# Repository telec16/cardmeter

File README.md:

# Cardmeter

The pleasure of having a multimeter in your pocket !

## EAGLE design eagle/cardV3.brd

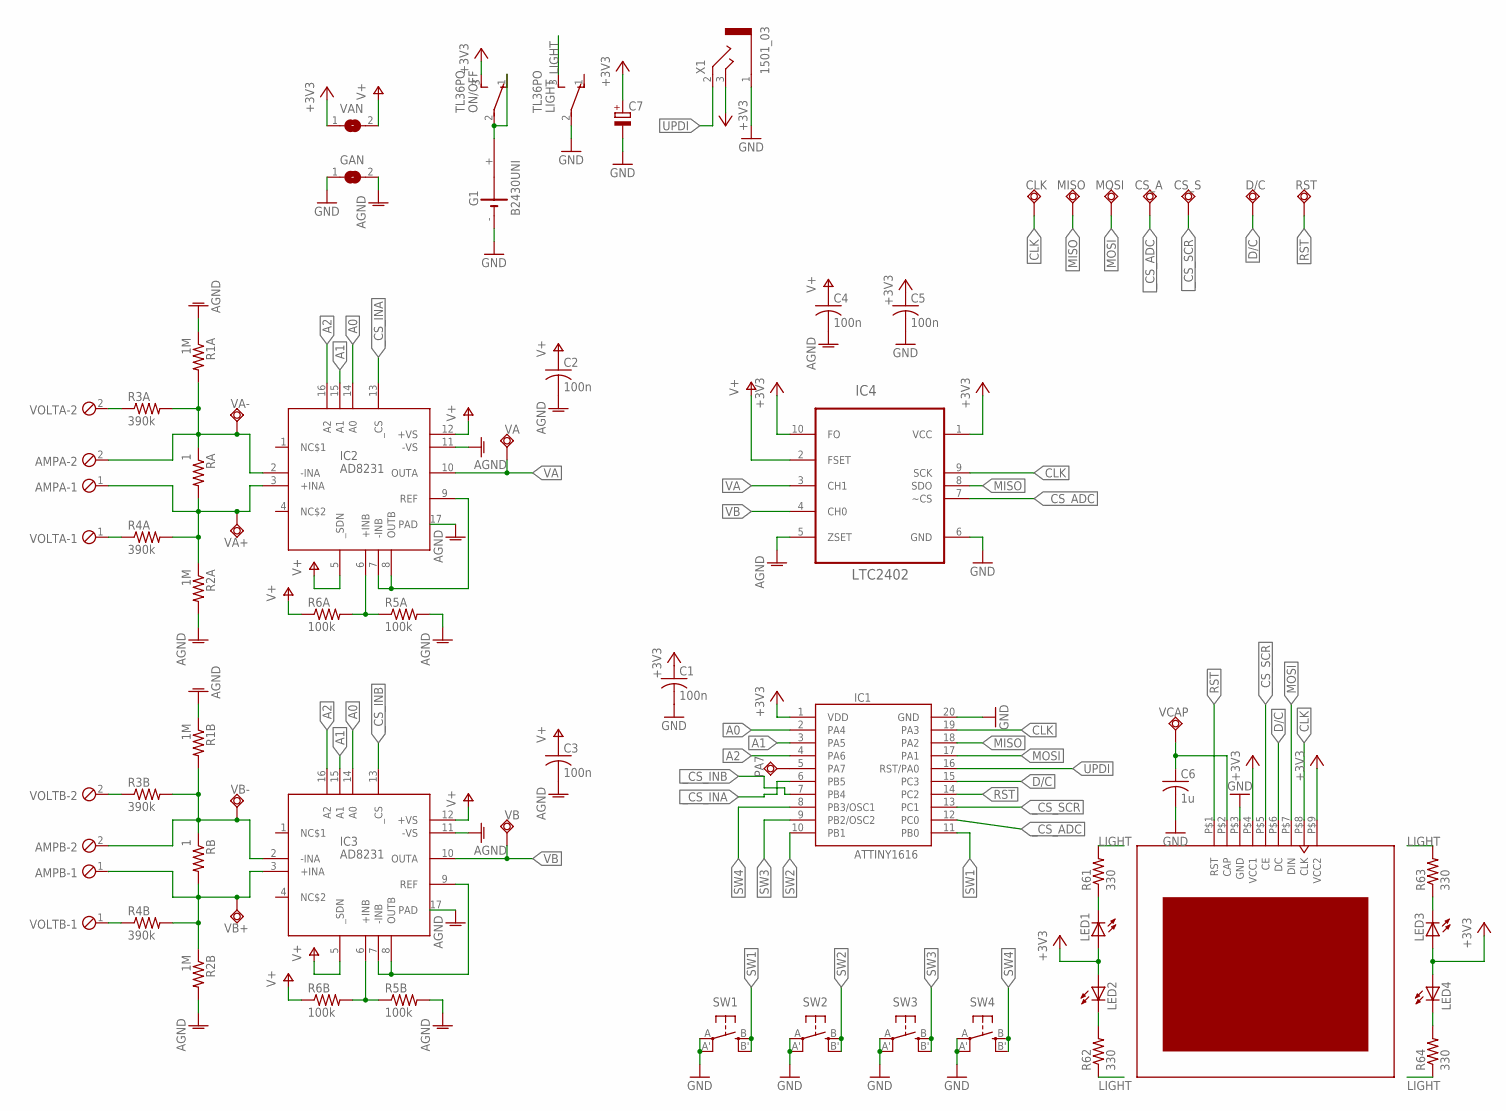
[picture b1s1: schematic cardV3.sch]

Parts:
AMPA: MPT2; 2POL254
AMPB: MPT2; 2POL254
C1, C2, C3, C4, C5: 100n; C0805K
C6: 1u; C0805
C7: CPOL-EU153CLV-0405; 153CLV-0405
CLK: TPSQB1,27; B1,27
CS_A: TPSQB1,27; B1,27
CS_S: TPSQB1,27; B1,27
D/C: TPSQB1,27; B1,27
G1: B2430UNI
GAN: SJ
IC1: ATTINY1616; SO20W
IC2, IC3: AD8231; LFCSP16
IC4: LTC2402; MSOP10
LED1, LED2, LED3, LED4: LEDCHIP-LED0805; CHIP-LED0805
LIGHT: TL36PO; TL3XPO
MISO: TPSQB1,27; B1,27
MOSI: TPSQB1,27; B1,27
ON/OFF: TL36PO; TL3XPO
PA7: TPSQB1,27; B1,27
R1A, R1B, R2A, R2B: 1M; M0805
R3A, R3B, R4A, R4B: 390k; M0805
R5A, R5B, R6A, R6B: 100k; M0805
R61, R62, R63, R64: 330; M0805
RA: 1; M0805
RB: 1; M0805
RST: TPSQB1,27; B1,27
SCR: NOKIA_SCREEN
SW1, SW2, SW3, SW4: SPST_TACT-EVQQ2; EVQ-Q2
VA: TPSQB1,27; B1,27
VA+: TPSQB1,27; B1,27
VA-: TPSQB1,27; B1,27
VAN: SJ
VB: TPSQB1,27; B1,27
VB+: TPSQB1,27; B1,27
VB-: TPSQB1,27; B1,27
VCAP: TPSQB1,27; B1,27
VOLTA: MPT2; 2POL254
VOLTB: MPT2; 2POL254
X1: 1501_03

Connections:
+3V3: C1.1, C5.1, C7.+, IC1.1 (VDD), IC4.1 (VCC), IC4.10 (FO), LED1.A, LED2.A, LED3.A, LED4.A, ON/OFF.3 (S), SCR.P$4 (VCC1), SCR.P$9 (VCC2), VAN.1, X1.3
A0: IC1.2 (PA4), IC2.14 (A0), IC3.14 (A0)
A1: IC1.3 (PA5), IC2.15 (A1), IC3.15 (A1)
A2: IC1.4 (PA6), IC2.16 (A2), IC3.16 (A2)
AGND: C2.2, C3.2, C4.2, GAN.2, IC2.11 (-VS), IC2.17 (PAD), IC3.11 (-VS), IC3.17 (PAD), IC4.5 (ZSET), R1A.1, R1B.1, R2A.2, R2B.2, R5A.2, R5B.2
CLK: CLK.TP, IC1.19 (PA3), IC4.9 (SCK), SCR.P$8 (CLK)
D/C: D/C.TP, IC1.15 (PC3), SCR.P$6 (DC)
GND: C1.2, C5.2, C6.2, C7.-, G1.-, GAN.1, IC1.20 (GND), IC4.6 (GND), LIGHT.2, SCR.P$3 (GND), SW1.A, SW1.A' (P1), SW2.A, SW2.A' (P1), SW3.A, SW3.A' (P1), SW4.A, SW4.A' (P1), X1.1
LIGHT: LIGHT.3 (S), R61.2, R62.1, R63.2, R64.1
MISO: IC1.18 (PA2), IC4.8 (SDO), MISO.TP
MOSI: IC1.17 (PA1), MOSI.TP, SCR.P$7 (DIN)
unnamed: G1.+, ON/OFF.1 (O), ON/OFF.2
unnamed: LED1.C, R61.1
unnamed: C6.1, SCR.P$2 (CAP), VCAP.TP
unnamed: LED2.C, R62.2
unnamed: LED4.C, R64.2
unnamed: LED3.C, R63.1
unnamed: R4A.1, VOLTA.1
unnamed: AMPB.2, IC3.2 (-INA), R1B.2, R3B.2, RB.1, VB-.TP
unnamed: AMPB.1, IC3.3 (+INA), R2B.1, R4B.2, RB.2, VB+.TP
unnamed: IC2.6 (+INB), R5A.1, R6A.2
unnamed: R3A.1, VOLTA.2
unnamed: AMPA.2, IC2.2 (-INA), R1A.2, R3A.2, RA.1, VA-.TP
unnamed: IC2.7 (-INB), IC2.8 (OUTB), IC2.9 (REF)
unnamed: AMPA.1, IC2.3 (+INA), R2A.1, R4A.2, RA.2, VA+.TP
unnamed: R3B.1, VOLTB.2
unnamed: IC3.7 (-INB), IC3.8 (OUTB), IC3.9 (REF)
unnamed: R4B.1, VOLTB.1
unnamed: IC3.6 (+INB), R5B.1, R6B.2
unnamed: IC1.5 (PA7), PA7.TP
RST: IC1.14 (PC2), RST.TP, SCR.P$1 (RST)
SW1: IC1.11 (PB0), SW1.B (S), SW1.B' (S1)
SW2: IC1.10 (PB1), SW2.B (S), SW2.B' (S1)
SW3: IC1.9 (PB2/OSC2), SW3.B (S), SW3.B' (S1)
SW4: IC1.8 (PB3/OSC1), SW4.B (S), SW4.B' (S1)
UPDI: IC1.16 (RST/PA0), X1.2
V+: C2.1, C3.1, C4.1, IC2.5 (_SDN), IC2.12 (+VS), IC3.5 (_SDN), IC3.12 (+VS), IC4.2 (FSET), R6A.1, R6B.1, VAN.2
VA: IC2.10 (OUTA), IC4.3 (CH1), VA.TP
VB: IC3.10 (OUTA), IC4.4 (CH0), VB.TP
_CS_ADC: CS_A.TP, IC1.12 (PC0), IC4.7 (~CS)
_CS_INA: IC1.6 (PB5), IC2.13 (_CS)
_CS_INB: IC1.7 (PB4), IC3.13 (_CS)
_CS_SCR: CS_S.TP, IC1.13 (PC1), SCR.P$5 (CE)

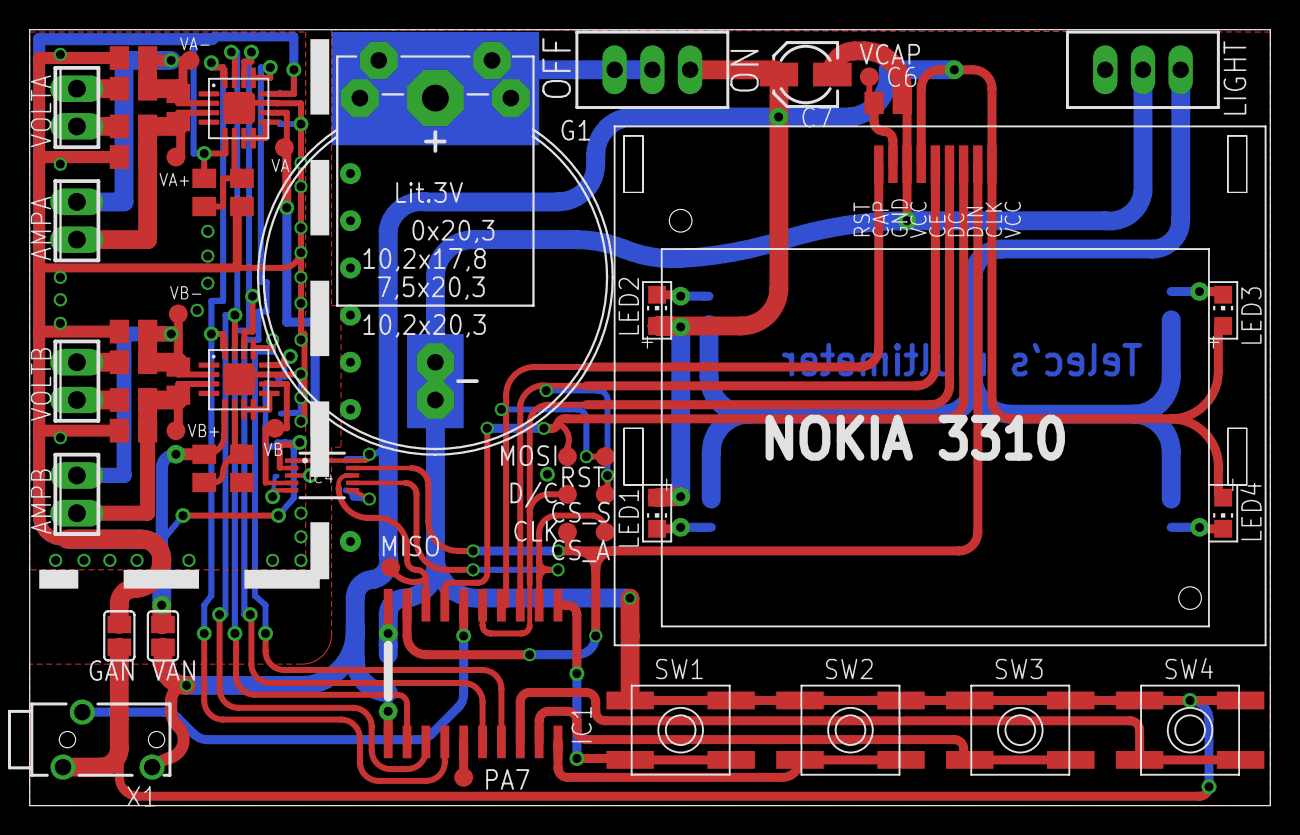
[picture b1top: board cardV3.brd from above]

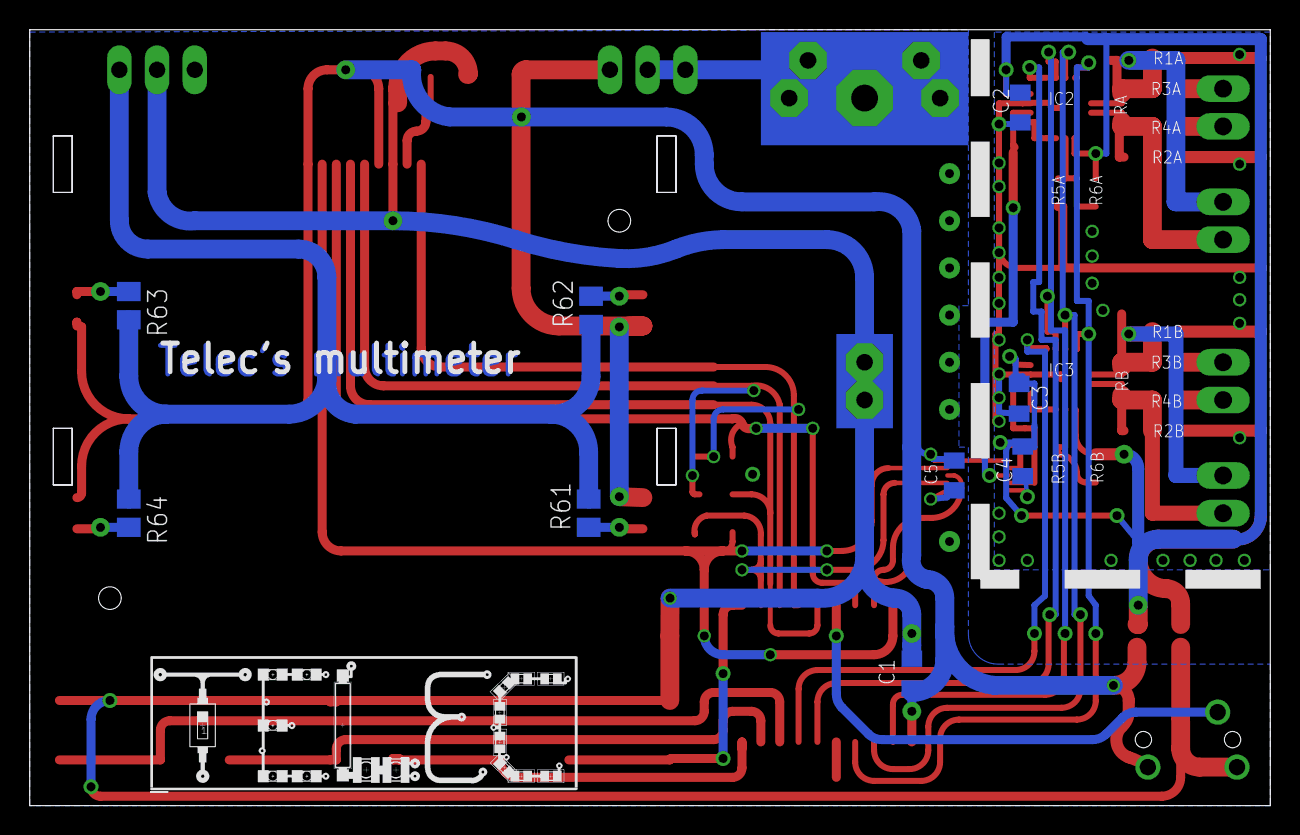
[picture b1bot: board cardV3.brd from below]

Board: 2 copper layers, 83.5 x 52.2 mm, 63 parts (9 on the bottom side), 43 nets.

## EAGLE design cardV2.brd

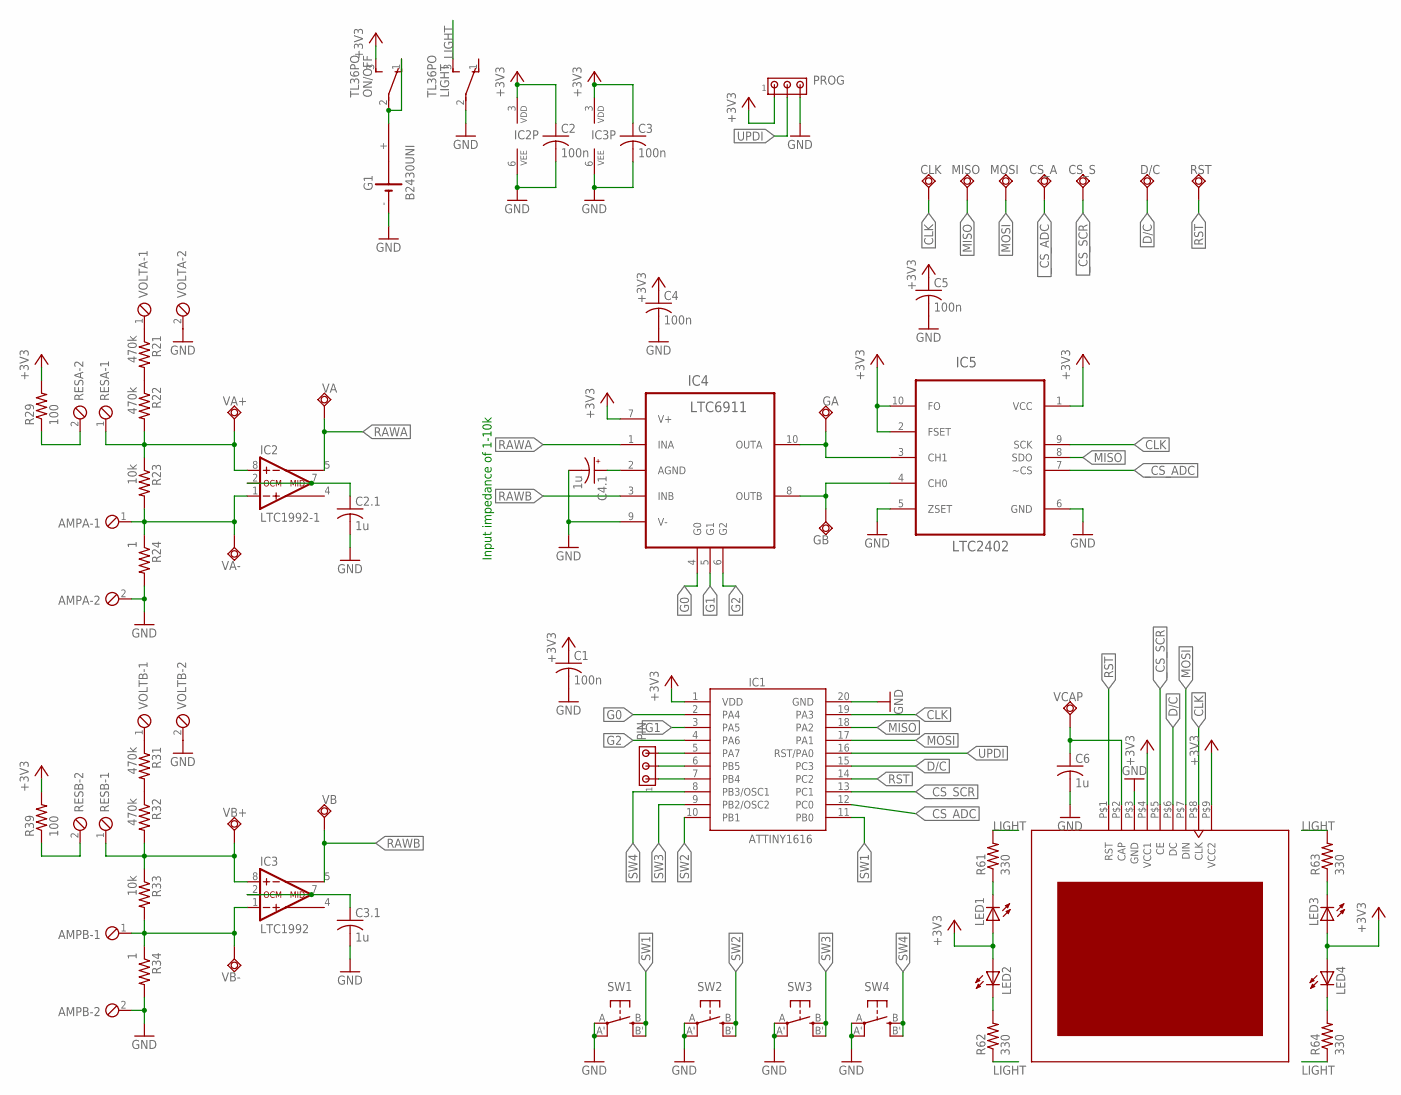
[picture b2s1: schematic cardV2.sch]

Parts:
AMPA: MPT2; 2POL254
AMPB: MPT2; 2POL254
C1, C2, C3, C4, C5: 100n; C0805K
C2.1, C3.1, C6: 1u; C0805
C4.1: 1u; A/3216-18R
CLK: TPSQB1,27; B1,27
CS_A: TPSQB1,27; B1,27
CS_S: TPSQB1,27; B1,27
D/C: TPSQB1,27; B1,27
G1: B2430UNI
GA: TPSQB1,27; B1,27
GB: TPSQB1,27; B1,27
IC1: ATTINY1616; SO20W
IC2: LTC1992-1; MSOP8
IC3: LTC1992; MSOP8
IC4: LTC6911; MSOP10
IC5: LTC2402; MSOP10
LED1, LED2, LED3, LED4: LEDCHIP-LED0805; CHIP-LED0805
LIGHT: TL36PO; TL3XPO
MISO: TPSQB1,27; B1,27
MOSI: TPSQB1,27; B1,27
ON/OFF: TL36PO; TL3XPO
PIN: MTA03-100; 10X03MTA
PROG: MTA03-100; 10X03MTA
R21, R22, R31, R32: 470k; M0805
R23, R33: 10k; M0805
R24, R34: 1; M0805
R29, R39: 100; M0805
R61, R62, R63, R64: 330; M0805
RESA: MPT2; 2POL254
RESB: MPT2; 2POL254
RST: TPSQB1,27; B1,27
SW1, SW2, SW3, SW4: SPST_TACT-EVQQ2; EVQ-Q2
U$1: NOKIA_SCREEN
VA: TPSQB1,27; B1,27
VA+: TPSQB1,27; B1,27
VA-: TPSQB1,27; B1,27
VB: TPSQB1,27; B1,27
VB+: TPSQB1,27; B1,27
VB-: TPSQB1,27; B1,27
VCAP: TPSQB1,27; B1,27
VOLTA: MPT2; 2POL254
VOLTB: MPT2; 2POL254

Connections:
CLK: CLK.TP, IC1.19 (PA3), IC5.9 (SCK), U$1.P$8 (CLK)
D/C: D/C.TP, IC1.15 (PC3), U$1.P$6 (DC)
G0: IC1.2 (PA4), IC4.4 (G0)
G1: IC1.3 (PA5), IC4.5 (G1)
G2: IC1.4 (PA6), IC4.6 (G2)
LIGHT: LIGHT.3 (S), R61.2, R62.1, R63.2, R64.1
MISO: IC1.18 (PA2), IC5.8 (SDO), MISO.TP
MOSI: IC1.17 (PA1), MOSI.TP, U$1.P$7 (DIN)
unnamed: G1.+, ON/OFF.1 (O), ON/OFF.2
unnamed: LED1.C, R61.1
unnamed: C6.1, U$1.P$2 (CAP), VCAP.TP
unnamed: LED2.C, R62.2
unnamed: LED4.C, R64.2
unnamed: LED3.C, R63.1
unnamed: IC1.7 (PB4), PIN.1
unnamed: IC1.5 (PA7), PIN.3
unnamed: IC1.6 (PB5), PIN.2
unnamed: AMPA.1, IC2.1 (-IN), R23.2, R24.1, VA-.TP
unnamed: IC2.8 (+IN), R22.2, R23.1, RESA.1, VA+.TP
unnamed: C4.1.+, IC4.2 (AGND)
unnamed: C2.1.1, IC2.2 (OCM), IC2.7 (MID)
unnamed: R21.2, R22.1
unnamed: AMPB.1, IC3.1 (-IN), R33.2, R34.1, VB-.TP
unnamed: IC3.8 (+IN), R32.2, R33.1, RESB.1, VB+.TP
unnamed: R21.1, VOLTA.1
unnamed: R29.1, RESA.2
unnamed: GB.TP, IC4.8 (OUTB), IC5.4 (CH0)
unnamed: C3.1.1, IC3.2 (OCM), IC3.7 (MID)
unnamed: R31.2, R32.1
unnamed: R31.1, VOLTB.1
unnamed: R39.1, RESB.2
unnamed: GA.TP, IC4.10 (OUTA), IC5.3 (CH1)
RAWA: IC2.5 (-OUT), IC4.1 (INA), VA.TP
RAWB: IC3.5 (-OUT), IC4.3 (INB), VB.TP
RST: IC1.14 (PC2), RST.TP, U$1.P$1 (RST)
SW1: IC1.11 (PB0), SW1.B (S), SW1.B' (S1)
SW2: IC1.10 (PB1), SW2.B (S), SW2.B' (S1)
SW3: IC1.9 (PB2/OSC2), SW3.B (S), SW3.B' (S1)
SW4: IC1.8 (PB3/OSC1), SW4.B (S), SW4.B' (S1)
UPDI: IC1.16 (RST/PA0), PROG.2
_CS_ADC: CS_A.TP, IC1.12 (PC0), IC5.7 (~CS)
_CS_SCR: CS_S.TP, IC1.13 (PC1), U$1.P$5 (CE)

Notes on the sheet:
Input impedance of 1-10k

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
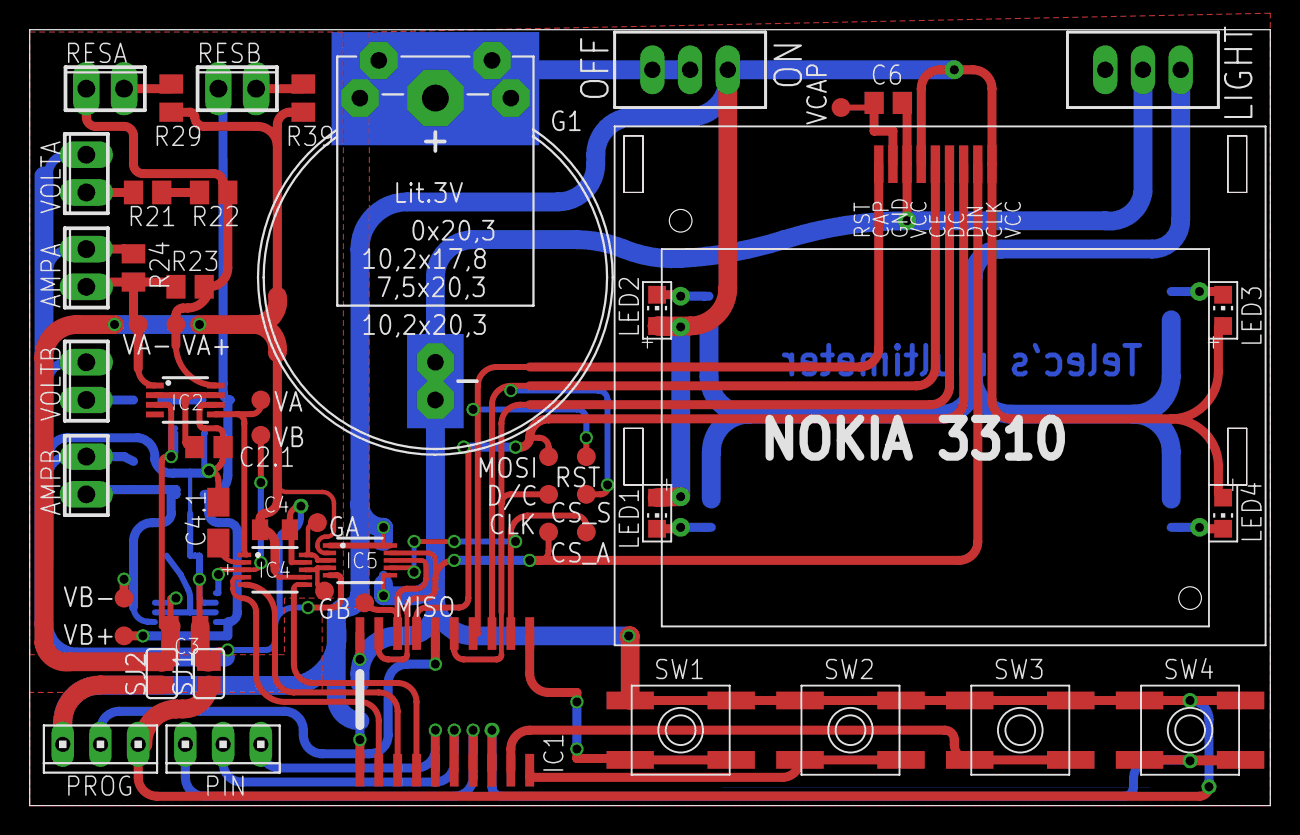
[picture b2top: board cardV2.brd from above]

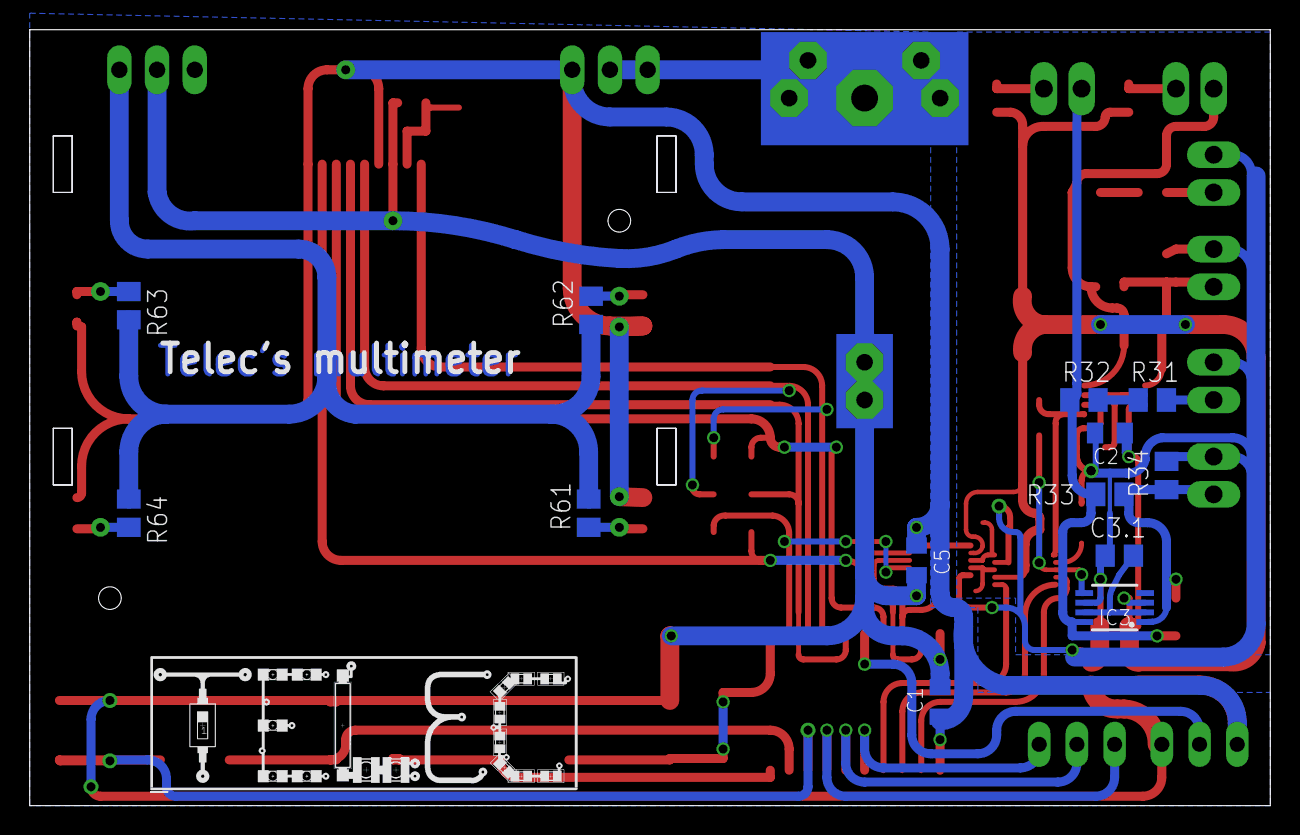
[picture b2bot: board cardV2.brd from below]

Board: 2 copper layers, 83.5 x 52.2 mm, 66 parts (13 on the bottom side), 46 nets.

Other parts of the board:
SJ1, SJ2: SJ

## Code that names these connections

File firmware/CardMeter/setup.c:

/*		____u___
 * VDD-|	A	|-GND
 * PA4-|	T	|-PA3
 * PA5-|	t	|-PA2
 * PA6-|	i	|-PA1
 * PA7-|	n	|-PA0
 * PB5-|	y	|-PC3
 * PB4-|	1	|-PC2
 * PB3-|	6	|-PC1
 * PB2-|	1	|-PC0
 * PB1-|____6___|-PB0
 */

#include "setup.h"

#define PULLUPEN (1<<3)
#define INVEN (1<<7)


#define OSC20M (0b00<<0)
#define PDIV2 (0b0000<<1)
#define PEN (1<<0)
#define PDIS (0<<0)

#define IOREG 0xD8


// Serial
const pin_t SCK = {.pin=3, .port=&VPORTA}; //PA3
const pin_t SDI = {.pin=2, .port=&VPORTA}; //PA2
const pin_t SDO = {.pin=1, .port=&VPORTA}; //PA1
const pin_t CS_SCR = {.pin=1, .port=&VPORTC}; //PC1
const pin_t CS_ADC = {.pin=0, .port=&VPORTC}; //PC0

// Gain
const pin_t CS_GAIN = {.pin=4, .port=&VPORTB}; //PB4

// Screen
const pin_t DC = {.pin=3, .port=&VPORTC}; //PC3
const pin_t RST = {.pin=2, .port=&VPORTC}; //PC2
	

void clockSetup()
{
	CCP = IOREG;
	CLKCTRL.MCLKCTRLA = OSC20M;
	
	CCP = IOREG;
	CLKCTRL.MCLKCTRLB = PDIV2 | PDIS;
	
	CCP = IOREG;
	CLKCTRL.MCLKLOCK = 1;
}
 
void pinSetup()
{
#if defined (V1)
	VPORTA.DIR = 0b01111010;
	VPORTB.DIR = 0b00000000;
	VPORTC.DIR = 0b00001111;
#elif defined (V2)
	VPORTA.DIR = 0b01111010;
	VPORTB.DIR = 0b00110000;
	VPORTC.DIR = 0b00001111;
#elif defined (V4)
	VPORTA.DIR = 0b10111100;
	VPORTB.DIR = 0b00100000;
	VPORTC.DIR = 0b00001110;
#elif defined (V5_F)
	VPORTA.DIR = 0b01111010;
	VPORTB.DIR = 0b00010000;
	VPORTC.DIR = 0b00001111;
	PORTA.PIN2CTRL = PULLUPEN;
	VPORTC.OUT = 0x3;
#endif
	
	PORTB.PIN0CTRL = PULLUPEN | INVEN;
	PORTB.PIN1CTRL = PULLUPEN | INVEN;
	PORTB.PIN2CTRL = PULLUPEN | INVEN;
	PORTB.PIN3CTRL = PULLUPEN | INVEN;
}

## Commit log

2018-02-11 V1.0
    This seems ok
2018-02-11 Added components values
2018-02-16 Updated design and curved traces
    Ready to ship !
2018-02-25 spaced a via
2018-03-10 Few changes, added logo
2018-03-11 Added missing dimension
2018-04-21 Code is here !
2018-04-22 Fixed .gitignore
2018-04-22 Something isn't working...
2018-05-07 Small changes in board V2 & more test in programming
    BTW the programm works, the problem came from the not well connected LCD
2018-05-07 Completly separated power lines (analog vs digital)
    And more program tests
2018-05-07 Oops forget to save, see last commit
2018-07-22 V3 will change everything
2018-07-22 Better V3...
2018-08-01 improvement
2020-01-23 Restructured repo
2020-01-23 front and is working
    Common Mode problem, probably due to resistor matching
2020-01-23 LTSpice files
2020-01-23 LTSpice tests
2020-04-17 fix: ugly readme
2020-05-09 Preparing for V5
2020-05-09 Added LTC2315 driver and some PORT/pin black magic
2020-05-09 finishing touches
    ADC is not working, more tests needed
2020-05-10 Trying to match more the spec
2020-05-10 UI base
2020-05-10 why I didn't saw that?
2020-05-10 Schematic for V5
2020-05-11 UI files
